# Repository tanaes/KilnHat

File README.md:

# KilnHat
PCB for running a kiln from a Raspberry Pi.

Has three MOSFET channels for controlling a mechanical safety relay, an SSR, and a fan. On-board thermocouple amplifier. Includes outputs for digital displays, addressable LEDs, and an I2C port.

*This is not yet a true 'hat' as I haven't yet implemented the full requirements!* However, my goal is to test the initial prototypes and add the required I2C EEPROM and over-voltage protection circuitry in a subsequent revision.

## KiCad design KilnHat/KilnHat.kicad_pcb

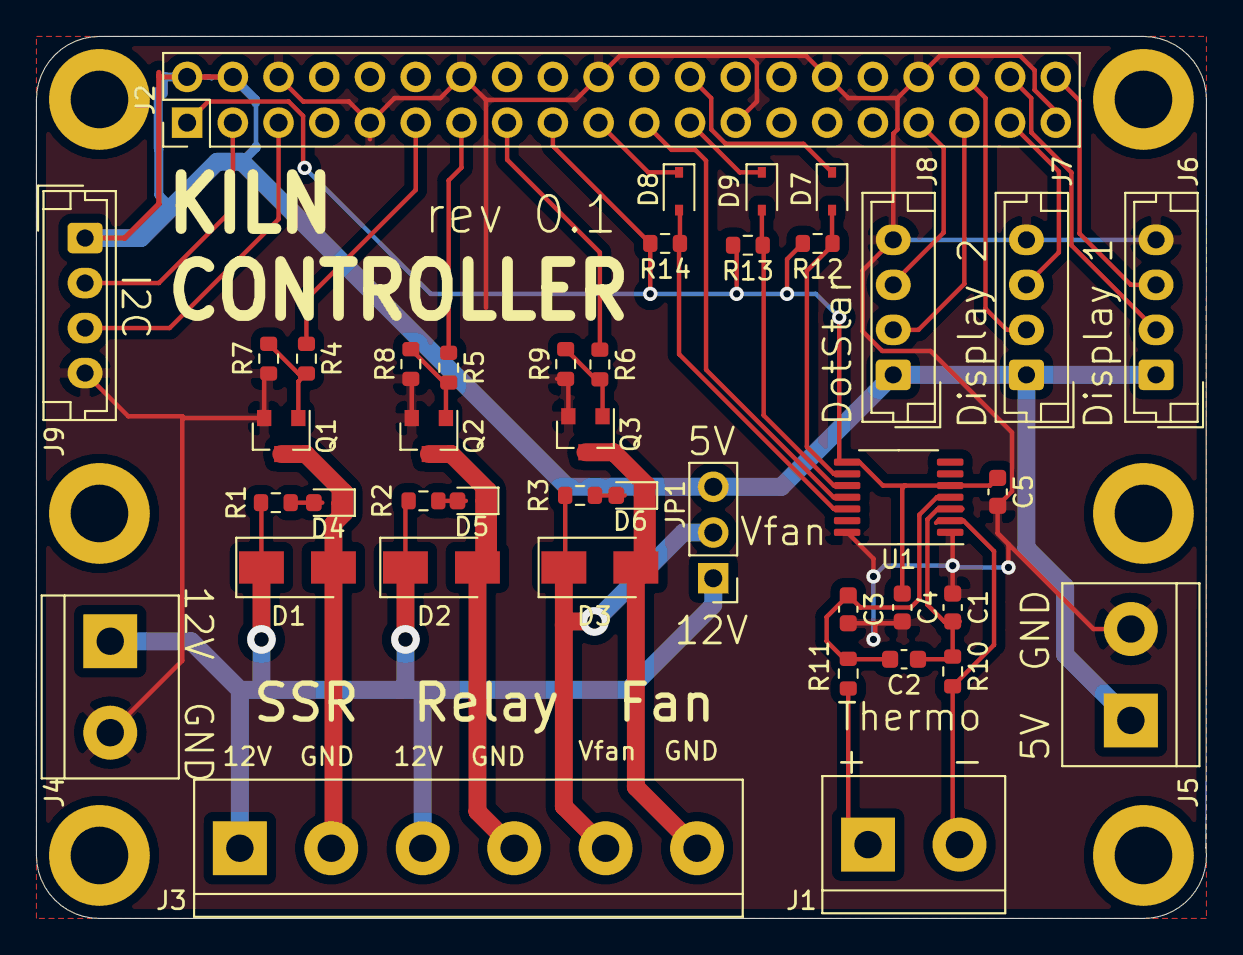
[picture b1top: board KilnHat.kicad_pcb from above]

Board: 2 copper layers, 65.0 x 49.0 mm, 42 parts (0 on the bottom side), 36 nets.

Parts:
C1, C3: .01uF; C_0603_1608Metric
C2, C4, C5: .1uF; C_0603_1608Metric
D1, D2, D3: D_Schottky; D_SMA
D4, D5, D6: LED; LED_0603_1608Metric
D7, D8, D9: 1N4148WS; D_SOD-323
J1: Screw_Terminal_01x02; TerminalBlock_bornier-2_P5.08mm
J2: Conn_02x20_Odd_Even; PinHeader_2x20_P2.54mm_Vertical
J3: Screw_Terminal_01x06; TerminalBlock_bornier-6_P5.08mm
J4: 12V PS in; TerminalBlock_bornier-2_P5.08mm
J5: 5V PS in; TerminalBlock_bornier-2_P5.08mm
J6: Disp1; JST_EH_B4B-EH-A_1x04_P2.50mm_Vertical
J7: Disp2; JST_EH_B4B-EH-A_1x04_P2.50mm_Vertical
J8: DotStar; JST_EH_B4B-EH-A_1x04_P2.50mm_Vertical
J9: I2C; JST_EH_B4B-EH-A_1x04_P2.50mm_Vertical
JP1: Jumper_3_Bridged12; PinHeader_1x03_P2.54mm_Vertical
Q1, Q2, Q3: AO3400A; SOT-23
R1, R2, R3: 4.7k; R_0603_1608Metric
R4, R5, R6, R10, R11: 100; R_0603_1608Metric
R7, R8, R9, R12, R13, R14: 10k; R_0603_1608Metric
U1: MAX31856; TSSOP-14_4.4x5mm_P0.65mm

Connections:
3V3: C4.1, C5.1, J2.1, J2.17, R12.2, R13.2, R14.2, U1.5, U1.8
5V: J2.2, J2.4, J5.1, J6.1, J7.1, J8.1, J9.1, JP1.3
+12V: D1.1, D2.1, J3.1, J3.3, J4.1, JP1.1, R1.2, R2.2
D1_CLK: J2.38, J6.2
D1_DAT: J2.40, J6.3
D2_CLK: J2.36, J7.2
D2_DAT: J2.37, J7.3
DOT_CLK: J2.35, J8.2
DOT_DAT: J2.33, J8.3
GND: C1.1, C3.2, C4.2, C5.2, J2.6, J2.9, J2.14, J2.20, J2.25, J2.30, J2.34, J2.39, J4.2, J5.2, J6.4, J7.4, J8.4, J9.4, Q1.2, Q2.2, Q3.2, R7.1, R8.1, R9.1, U1.1, U1.14
unnamed: C1.2, C2.1, R10.1, U1.3
unnamed: C2.2, C3.1, R11.1, U1.4
unnamed: D4.2, R1.1
unnamed: D5.2, R2.1
unnamed: D6.2, R3.1
unnamed: D7.2, R12.1, U1.9
unnamed: D8.2, R14.1, U1.12
unnamed: D9.2, R13.1, U1.10
unnamed: J1.1, R11.2
unnamed: J1.2, R10.2, U1.2
unnamed: Q1.1, R4.2, R7.2
unnamed: Q2.1, R5.2, R8.2
unnamed: Q3.1, R6.2, R9.2
SCL1_I2C: J2.5, J9.3
SDA1_I2C: J2.3, J9.2
SPI0_CS0: D7.1, J2.24
SPI0_MISO: J2.21, U1.11
SPI0_MOSI: D8.1, J2.19
SPI0_SCLK: D9.1, J2.23
Vfan: D3.1, J3.5, JP1.2, R3.2
mosfet0: D1.2, D4.1, J3.2, Q1.3
mosfet1: D2.2, D5.1, J3.4, Q2.3
mosfet2: D3.2, D6.1, J3.6, Q3.3
pwm0: J2.11, R4.1
pwm1: J2.13, R5.1
pwm2: J2.15, R6.1

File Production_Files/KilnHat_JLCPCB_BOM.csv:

Comment,Designator,Footprint,LCSC Part #
".01uF Unpolarized capacitor, small symbol","C1,C3",C_0603_1608Metric,0603
".1uF Unpolarized capacitor, small symbol","C2,C4,C5",C_0603_1608Metric,C14663
D_Schottky Schottky diode,"D1,D2,D3",D_SMA,C22452
LED Light emitting diode,"D4,D5,D6",LED_0603_1608Metric,C2286
"1N4148WS 75V 0.15A Fast switching Diode, SOD-323","D7,D8,D9",D_SOD-323,C2128
"AO3400A 50V Vds, 0.22A Id, N-Channel MOSFET, SOT-23","Q1,Q2,Q3",SOT-23,C20917
4.7k Resistor,"R1,R2,R3",R_0603_1608Metric,C23162
100 Resistor,"R4,R5,R6,R10,R11",R_0603_1608Metric,C22775
10k Resistor,"R7,R8,R9,R12,R13,R14",R_0603_1608Metric,C25804

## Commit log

2021-10-04 added files
2021-10-04 typo
